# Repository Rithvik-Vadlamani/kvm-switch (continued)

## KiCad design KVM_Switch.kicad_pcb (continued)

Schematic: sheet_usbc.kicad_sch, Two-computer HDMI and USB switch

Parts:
C10, C11, C12, C13, C14, C15: 0.1uF; C_0402_1005Metric; Voltage 50V; MPN CC0402KRX7R9BB104; LCSC Part C131394
C47, C48: 100nF; C_0402_1005Metric; Voltage 50V; MPN CC0402KRX7R9BB104; LCSC Part C131394
C49, C50: 1uF; C_0603_1608Metric; Voltage 16V; MPN CL10B105KO8NNNC; LCSC Part C59782
J1, J2: USB4105-GF-A-120; USB_C_Receptacle_GCT_USB4105-xx-A_16P_TopMnt_Horizontal; MPN USB4105-GF-A-120; LCSC Part C5184243
J_HDMI_C1_MON1: HDMI_A_1.4; Assembly_J_HDMI_C1_MON1; MPN 2086581001; LCSC Part C916313
J_HDMI_C1_MON2: HDMI_A_1.4; Assembly_J_HDMI_C1_MON2; MPN 2086581001; LCSC Part C916313
J_HDMI_C2_MON1: HDMI_A_1.4; Assembly_J_HDMI_C2_MON1; MPN 2086581001; LCSC Part C916313
J_HDMI_C2_MON2: HDMI_A_1.4; Assembly_J_HDMI_C2_MON2; MPN 2086581001; LCSC Part C916313
J_HDMI_MON1: HDMI_A_1.4; Assembly_J_HDMI_MON1; MPN 2086581001; LCSC Part C916313
J_HDMI_MON2: HDMI_A_1.4; Assembly_J_HDMI_MON2; MPN 2086581001; LCSC Part C916313
R6, R14, R15, R16: 47k; R_0402_1005Metric; Tolerance 1%; MPN 0402WGF4702TCE; LCSC Part C25792
R7, R8, R9, R10: 5.1k; R_0402_1005Metric; Tolerance 1%; MPN 0402WGF5101TCE; LCSC Part C25905
R17, R18, R19, R20: 100k; R_0402_1005Metric; Tolerance 1%; MPN 0402WGF1003TCE; LCSC Part C25741
R43, R45: 10k; R_0402_1005Metric; Tolerance 1%; MPN 0402WGF1002TCE; LCSC Part C25744
R44: 10k; Assembly_R44; Tolerance 1%; MPN 0402WGF1002TCE; LCSC Part C25744
R46: 10k; Assembly_R46; Tolerance 1%; MPN 0402WGF1002TCE; LCSC Part C25744
R47, R48: 210k; R_0402_1005Metric; Tolerance 1%; MPN AF0402FR-07210KL; LCSC Part C20143942
U4, U5, U7, U11, U12, U13, U14, U15, U16, U17, U18, U19: TPD4E02B04DQA; USON-10_2.5x1.0mm_P0.5mm_Assembly; MPN TPD4E02B04DQAR; LCSC Part C106794
U6, U8: HD3SS215IRTQR; QFN-56-1EP_8x8mm_P0.5mm_EP4.5x5.2mm_ThermalVias; MPN HD3SS215IRTQT; LCSC Part C2674402
U24, U25, U26, U27, U28, U29, U30, U31: TPD4E05U06DQAR; USON-10_2.5x1.0mm_P0.5mm_Assembly; MPN TPD4E05U06DQAR; LCSC Part C138714
U32, U33: TPS2553DBVR; SOT-23-6; MPN TPS2553DBVR; LCSC Part C55266

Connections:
+3.3V: C10.1, C11.1, C12.1, C13.1, C14.1, C15.1, R43.1, R45.1, U6.19 (VDD), U6.55 (VDD), U8.19 (VDD), U8.55 (VDD), U32.3 (EN), U33.3 (EN); also elsewhere on the board
+5V: C47.1, C48.1, U32.1 (IN), U33.1 (IN); also elsewhere on the board
/USBC_Mux/C1_MON1_D0_N: J_HDMI_C1_MON1.9 (D0-), U6.47 (DA2(n)), U13.2 (IO2), U13.9 (NC)
/USBC_Mux/C1_MON1_D0_P: J_HDMI_C1_MON1.7 (D0+), U6.48 (DA2(p)), U13.1 (IO1), U13.10 (NC)
/USBC_Mux/C1_MON1_D1_N: J_HDMI_C1_MON1.6 (D1-), U6.50 (DA1(n)), U12.5 (IO4), U12.6 (NC)
/USBC_Mux/C1_MON1_D1_P: J_HDMI_C1_MON1.4 (D1+), U6.51 (DA1(p)), U12.4 (IO3), U12.7 (NC)
/USBC_Mux/C1_MON1_D2_N: J_HDMI_C1_MON1.3 (D2-), U6.53 (DA0(n)), U12.2 (IO2), U12.9 (NC)
/USBC_Mux/C1_MON1_D2_P: J_HDMI_C1_MON1.1 (D2+), U6.54 (DA0(p)), U12.1 (IO1), U12.10 (NC)
/USBC_Mux/C1_MON1_D3_N: J_HDMI_C1_MON1.12 (CK-), U6.44 (DA3(n)), U13.5 (IO4), U13.6 (NC)
/USBC_Mux/C1_MON1_D3_P: J_HDMI_C1_MON1.10 (CK+), U6.45 (DA3(p)), U13.4 (IO3), U13.7 (NC)
/USBC_Mux/C1_MON1_DDC_CLK: J_HDMI_C1_MON1.15 (SCL), U6.27 (DDCCLK_A), U26.1 (IO1)
/USBC_Mux/C1_MON1_DDC_DAT: J_HDMI_C1_MON1.16 (SDA), U6.28 (DDCDAT_A), U26.2 (IO2)
/USBC_Mux/C1_MON1_HPD: J_HDMI_C1_MON1.19 (HPD/HEAC-), R17.1, U6.16 (HPDA), U26.4 (IO3)
/USBC_Mux/C1_MON2_D0_N: J_HDMI_C1_MON2.9 (D0-), U8.51 (DA1(p)), U17.2 (IO2), U17.9 (NC)
/USBC_Mux/C1_MON2_D0_P: J_HDMI_C1_MON2.7 (D0+), U8.50 (DA1(n)), U17.1 (IO1), U17.10 (NC)
/USBC_Mux/C1_MON2_D1_N: J_HDMI_C1_MON2.6 (D1-), U8.48 (DA2(p)), U16.5 (IO4), U16.6 (NC)
/USBC_Mux/C1_MON2_D1_P: J_HDMI_C1_MON2.4 (D1+), U8.47 (DA2(n)), U16.4 (IO3), U16.7 (NC)
/USBC_Mux/C1_MON2_D2_N: J_HDMI_C1_MON2.3 (D2-), U8.45 (DA3(p)), U16.2 (IO2), U16.9 (NC)
/USBC_Mux/C1_MON2_D2_P: J_HDMI_C1_MON2.1 (D2+), U8.44 (DA3(n)), U16.1 (IO1), U16.10 (NC)
/USBC_Mux/C1_MON2_D3_N: J_HDMI_C1_MON2.12 (CK-), U8.54 (DA0(p)), U17.5 (IO4), U17.6 (NC)
/USBC_Mux/C1_MON2_D3_P: J_HDMI_C1_MON2.10 (CK+), U8.53 (DA0(n)), U17.4 (IO3), U17.7 (NC)
/USBC_Mux/C1_MON2_DDC_CLK: J_HDMI_C1_MON2.15 (SCL), U8.27 (DDCCLK_A), U28.1 (IO1)
/USBC_Mux/C1_MON2_DDC_DAT: J_HDMI_C1_MON2.16 (SDA), U8.28 (DDCDAT_A), U28.2 (IO2), U28.9 (NC)
/USBC_Mux/C1_MON2_HPD: J_HDMI_C1_MON2.19 (HPD/HEAC-), R19.1, U8.16 (HPDA), U28.4 (IO3)
/USBC_Mux/C2_MON1_D0_N: J_HDMI_C2_MON1.9 (D0-), U6.34 (DB2(n)), U15.2 (IO2), U15.9 (NC)
/USBC_Mux/C2_MON1_D0_P: J_HDMI_C2_MON1.7 (D0+), U6.35 (DB2(p)), U15.1 (IO1), U15.10 (NC)
/USBC_Mux/C2_MON1_D1_N: J_HDMI_C2_MON1.6 (D1-), U6.37 (DB1(n)), U14.5 (IO4), U14.6 (NC)
/USBC_Mux/C2_MON1_D1_P: J_HDMI_C2_MON1.4 (D1+), U6.38 (DB1(p)), U14.4 (IO3), U14.7 (NC)
/USBC_Mux/C2_MON1_D2_N: J_HDMI_C2_MON1.3 (D2-), U6.40 (DB0(n)), U14.2 (IO2), U14.9 (NC)
/USBC_Mux/C2_MON1_D2_P: J_HDMI_C2_MON1.1 (D2+), U6.41 (DB0(p)), U14.1 (IO1), U14.10 (NC)
/USBC_Mux/C2_MON1_D3_N: J_HDMI_C2_MON1.12 (CK-), U6.31 (DB3(n)), U15.5 (IO4), U15.6 (NC)
/USBC_Mux/C2_MON1_D3_P: J_HDMI_C2_MON1.10 (CK+), U6.32 (DB3(p)), U15.4 (IO3), U15.7 (NC)
/USBC_Mux/C2_MON1_DDC_CLK: J_HDMI_C2_MON1.15 (SCL), U6.22 (DDCCLK_B), U27.1 (IO1)
/USBC_Mux/C2_MON1_DDC_DAT: J_HDMI_C2_MON1.16 (SDA), U6.23 (DDCDAT_B), U27.2 (IO2)
/USBC_Mux/C2_MON1_HPD: J_HDMI_C2_MON1.19 (HPD/HEAC-), R18.1, U6.17 (HPDB), U27.4 (IO3)
/USBC_Mux/C2_MON2_D0_N: J_HDMI_C2_MON2.9 (D0-), U8.38 (DB1(p)), U19.2 (IO2), U19.9 (NC)
/USBC_Mux/C2_MON2_D0_P: J_HDMI_C2_MON2.7 (D0+), U8.37 (DB1(n)), U19.1 (IO1), U19.10 (NC)
/USBC_Mux/C2_MON2_D1_N: J_HDMI_C2_MON2.6 (D1-), U8.35 (DB2(p)), U18.5 (IO4), U18.6 (NC)
/USBC_Mux/C2_MON2_D1_P: J_HDMI_C2_MON2.4 (D1+), U8.34 (DB2(n)), U18.4 (IO3), U18.7 (NC)
/USBC_Mux/C2_MON2_D2_N: J_HDMI_C2_MON2.3 (D2-), U8.32 (DB3(p)), U18.2 (IO2), U18.9 (NC)
/USBC_Mux/C2_MON2_D2_P: J_HDMI_C2_MON2.1 (D2+), U8.31 (DB3(n)), U18.1 (IO1), U18.10 (NC)
/USBC_Mux/C2_MON2_D3_N: J_HDMI_C2_MON2.12 (CK-), U8.41 (DB0(p)), U19.5 (IO4), U19.6 (NC)
/USBC_Mux/C2_MON2_D3_P: J_HDMI_C2_MON2.10 (CK+), U8.40 (DB0(n)), U19.4 (IO3), U19.7 (NC)
/USBC_Mux/C2_MON2_DDC_CLK: J_HDMI_C2_MON2.15 (SCL), U8.22 (DDCCLK_B), U29.1 (IO1)
/USBC_Mux/C2_MON2_DDC_DAT: J_HDMI_C2_MON2.16 (SDA), U8.23 (DDCDAT_B), U29.2 (IO2)
/USBC_Mux/C2_MON2_HPD: J_HDMI_C2_MON2.19 (HPD/HEAC-), R20.1, U8.17 (HPDB), U29.4 (IO3)
/USBC_Mux/MON1_D0_N: J_HDMI_MON1.9 (D0-), U5.2 (IO2), U5.9 (NC), U6.9 (DC2(n))
/USBC_Mux/MON1_D0_P: J_HDMI_MON1.7 (D0+), U5.1 (IO1), U5.10 (NC), U6.8 (DC2(p))
/USBC_Mux/MON1_D1_N: J_HDMI_MON1.6 (D1-), U4.5 (IO4), U4.6 (NC), U6.6 (DC1(n))
/USBC_Mux/MON1_D1_P: J_HDMI_MON1.4 (D1+), U4.4 (IO3), U4.7 (NC), U6.5 (DC1(p))
/USBC_Mux/MON1_D2_N: J_HDMI_MON1.3 (D2-), U4.2 (IO2), U4.9 (NC), U6.3 (DC0(n))
/USBC_Mux/MON1_D2_P: J_HDMI_MON1.1 (D2+), U4.1 (IO1), U4.10 (NC), U6.2 (DC0(p))
/USBC_Mux/MON1_D3_N: J_HDMI_MON1.12 (CK-), U5.5 (IO4), U5.6 (NC), U6.12 (DC3(n))
/USBC_Mux/MON1_D3_P: J_HDMI_MON1.10 (CK+), U5.4 (IO3), U5.7 (NC), U6.11 (DC3(p))
/USBC_Mux/MON1_DDC_CLK: J_HDMI_MON1.15 (SCL), R6.1, U6.18 (DDCCLK_C), U30.1 (IO1)
/USBC_Mux/MON1_DDC_DAT: J_HDMI_MON1.16 (SDA), R14.1, U6.26 (DDCDAT_C), U30.2 (IO2)
/USBC_Mux/MON1_HPD: J_HDMI_MON1.19 (HPD/HEAC-), U6.15 (HPDC), U30.4 (IO3)
/USBC_Mux/MON2_D0_N: J_HDMI_MON2.9 (D0-), U8.5 (DC1(p)), U11.2 (IO2), U11.9 (NC)
/USBC_Mux/MON2_D0_P: J_HDMI_MON2.7 (D0+), U8.6 (DC1(n)), U11.1 (IO1), U11.10 (NC)
/USBC_Mux/MON2_D1_N: J_HDMI_MON2.6 (D1-), U7.5 (IO4), U7.6 (NC), U8.8 (DC2(p))
/USBC_Mux/MON2_D1_P: J_HDMI_MON2.4 (D1+), U7.4 (IO3), U7.7 (NC), U8.9 (DC2(n))
/USBC_Mux/MON2_D2_N: J_HDMI_MON2.3 (D2-), U7.2 (IO2), U7.9 (NC), U8.11 (DC3(p))
/USBC_Mux/MON2_D2_P: J_HDMI_MON2.1 (D2+), U7.1 (IO1), U7.10 (NC), U8.12 (DC3(n))
/USBC_Mux/MON2_D3_N: J_HDMI_MON2.12 (CK-), U8.2 (DC0(p)), U11.5 (IO4), U11.6 (NC)
/USBC_Mux/MON2_D3_P: J_HDMI_MON2.10 (CK+), U8.3 (DC0(n)), U11.4 (IO3), U11.7 (NC)
/USBC_Mux/MON2_DDC_CLK: J_HDMI_MON2.15 (SCL), R15.1, U8.18 (DDCCLK_C), U31.1 (IO1)
/USBC_Mux/MON2_DDC_DAT: J_HDMI_MON2.16 (SDA), R16.1, U8.26 (DDCDAT_C), U31.2 (IO2)
/USBC_Mux/MON2_HPD: J_HDMI_MON2.19 (HPD/HEAC-), U8.15 (HPDC), U31.4 (IO3)
GND: C10.2, C11.2, C12.2, C13.2, C14.2, C15.2, C47.2, C48.2, C49.2, C50.2, J1.A1 (GND), J1.A12 (GND), J1.B1 (GND), J1.B12 (GND), J1.SH (SHIELD), J2.A1 (GND), J2.A12 (GND), J2.B1 (GND), J2.B12 (GND), J2.SH (SHIELD), J_HDMI_C1_MON1.2 (D2S), J_HDMI_C1_MON1.5 (D1S), J_HDMI_C1_MON1.8 (D0S), J_HDMI_C1_MON1.11 (CKS), J_HDMI_C1_MON1.17 (GND), J_HDMI_C1_MON1.SH, J_HDMI_C1_MON2.2 (D2S), J_HDMI_C1_MON2.5 (D1S), J_HDMI_C1_MON2.8 (D0S), J_HDMI_C1_MON2.11 (CKS), J_HDMI_C1_MON2.17 (GND), J_HDMI_C1_MON2.SH, J_HDMI_C2_MON1.2 (D2S), J_HDMI_C2_MON1.5 (D1S), J_HDMI_C2_MON1.8 (D0S), J_HDMI_C2_MON1.11 (CKS), J_HDMI_C2_MON1.17 (GND), J_HDMI_C2_MON1.SH, J_HDMI_C2_MON2.2 (D2S), J_HDMI_C2_MON2.5 (D1S), J_HDMI_C2_MON2.8 (D0S), J_HDMI_C2_MON2.11 (CKS), J_HDMI_C2_MON2.17 (GND), J_HDMI_C2_MON2.SH, J_HDMI_MON1.2 (D2S), J_HDMI_MON1.5 (D1S), J_HDMI_MON1.8 (D0S), J_HDMI_MON1.11 (CKS), J_HDMI_MON1.17 (GND), J_HDMI_MON1.SH, J_HDMI_MON2.2 (D2S), J_HDMI_MON2.5 (D1S), J_HDMI_MON2.8 (D0S), J_HDMI_MON2.11 (CKS), J_HDMI_MON2.17 (GND), J_HDMI_MON2.SH, R7.2, R8.2, R9.2, R10.2, R17.2, R18.2, R19.2, R20.2, R44.2, R46.2, R47.2, R48.2, U4.3 (G), U4.8 (G), U5.3 (G), U5.8 (G), U6.4 (GND), U6.7 (GND), U6.10 (GND), U6.33 (GND), U6.36 (GND), U6.39 (GND), U6.46 (GND), U6.49 (GND), U6.52 (GND), U6.57 (PAD), U7.3 (G), U7.8 (G), U8.4 (GND), U8.7 (GND), U8.10 (GND), U8.33 (GND), U8.36 (GND), U8.39 (GND), U8.46 (GND), U8.49 (GND), U8.52 (GND), U8.57 (PAD), U11.3 (G), U11.8 (G), U12.3 (G), U12.8 (G), U13.3 (G), U13.8 (G), U14.3 (G), U14.8 (G), U15.3 (G), U15.8 (G), U16.3 (G), U16.8 (G), U17.3 (G), U17.8 (G), U18.3 (G), U18.8 (G), U19.3 (G), U19.8 (G), U24.3 (G), U24.8 (G), U25.3 (G), U25.8 (G), U26.3 (G), U26.8 (G), U27.3 (G), U27.8 (G), U28.3 (G), U28.8 (G), U29.3 (G), U29.8 (G), U30.3 (G), U30.8 (G), U31.3 (G), U31.8 (G), U32.2 (GND), U33.2 (GND); also elsewhere on the board
HDMI_ILIM1: R47.1, U32.5 (ILIM)
HDMI_ILIM2: R48.1, U33.5 (ILIM)
HDMI_MODE_1: R43.2, R44.1, U6.1 (AUX_SEL)
HDMI_MODE_2: R45.2, R46.1, U8.1 (AUX_SEL)
HDMI_MON1_5V: C49.1, J_HDMI_MON1.18 (+5V), R6.2, R14.2, U32.6 (OUT)
HDMI_MON2_5V: C50.1, J_HDMI_MON2.18 (+5V), R15.2, R16.2, U33.6 (OUT)
HOST1_CC1: J1.A5 (CC1), R9.1, U24.4 (IO3), U24.7 (NC)
HOST1_CC2: J1.B5 (CC2), R10.1, U24.5 (IO4)
HOST1_VBUS: J1.A4 (VBUS), J1.A9 (VBUS), J1.B4 (VBUS), J1.B9 (VBUS); also elsewhere on the board
HOST2_CC1: J2.A5 (CC1), R7.1, U25.4 (IO3), U25.7 (NC)
HOST2_CC2: J2.B5 (CC2), R8.1, U25.5 (IO4)
HOST2_VBUS: J2.A4 (VBUS), J2.A9 (VBUS), J2.B4 (VBUS), J2.B9 (VBUS); also elsewhere on the board
HOST_SELECT: U6.56 (Dx_SEL), U8.56 (Dx_SEL); also elsewhere on the board
MUX_RESET: U6.43 (OE), U8.43 (OE); also elsewhere on the board
USB_HOST1_N: J1.A7 (D-), J1.B7 (D-), U24.2 (IO2), U24.9 (NC); also elsewhere on the board
USB_HOST1_P: J1.A6 (D+), J1.B6 (D+), U24.1 (IO1), U24.10 (NC); also elsewhere on the board
USB_HOST2_N: J2.A7 (D-), J2.B7 (D-), U25.2 (IO2), U25.9 (NC); also elsewhere on the board
USB_HOST2_P: J2.A6 (D+), J2.B6 (D+), U25.1 (IO1), U25.10 (NC); also elsewhere on the board

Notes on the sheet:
HDMI mode: AUX_SEL must be VDD/2. 10k/10k dividers; never leave AUX_SEL floating (TI datasheet section 7.5).
External-port ESD: 5.5V-rated arrays on USB D+/D-/CC and HDMI DDC/HPD. TPD4E02B04 arrays remain on the eight TMDS conductors of each HDMI connector.
HDMI input pin 18 rails are isolated from board +5V and from each other.

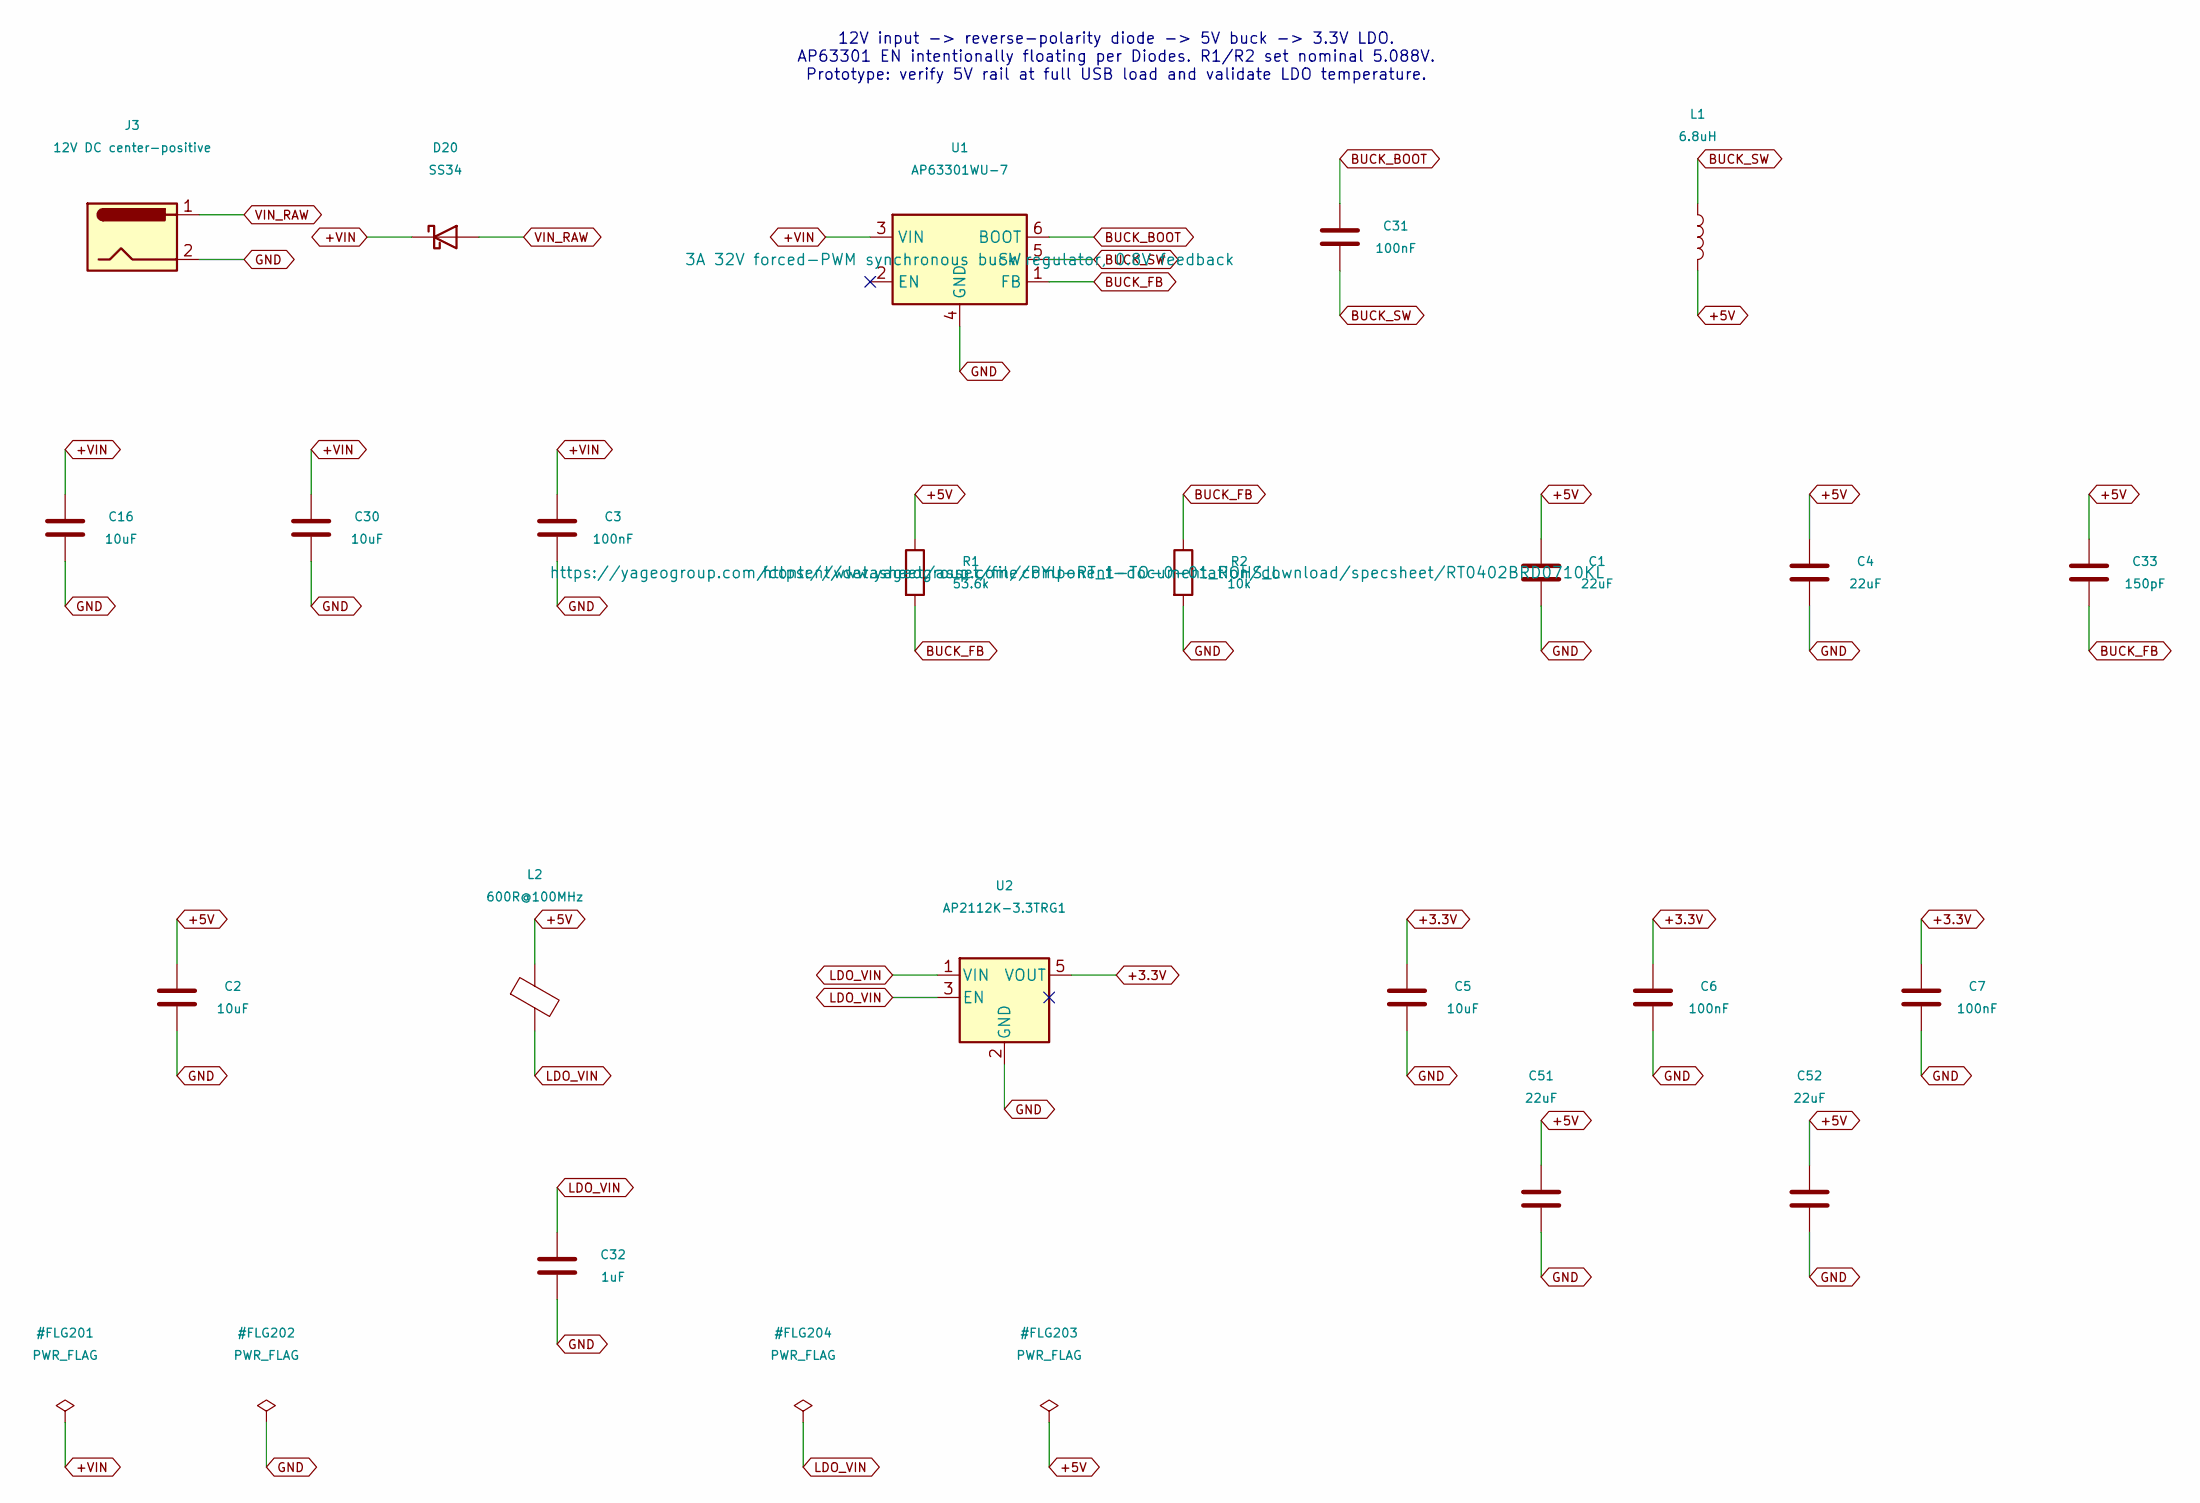
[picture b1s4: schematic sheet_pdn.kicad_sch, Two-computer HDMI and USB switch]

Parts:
C1, C4, C51, C52: 22uF; C_1206_3216Metric; Voltage 25V; MPN CL31A226KAHNNNE; LCSC Part C12891
C2, C5: 10uF; C_0805_2012Metric; Voltage 16V; MPN CL21B106KOQNNNE; LCSC Part C95841
C3, C6, C7, C31: 100nF; C_0402_1005Metric; Voltage 50V; MPN CC0402KRX7R9BB104; LCSC Part C131394
C16, C30: 10uF; C_1206_3216Metric; Voltage 50V; MPN CL31B106KBHNNNE; LCSC Part C89632
C32: 1uF; C_0603_1608Metric; Voltage 16V; MPN CL10B105KO8NNNC; LCSC Part C59782
C33: 150pF; C_0402_1005Metric; Voltage 50V; Tolerance 5%; MPN CL05C151JB5NNNC; LCSC Part C86286
D20: SS34; D_SMA; Rating 40V 3A; reverse-polarity isolation; MPN SS34; LCSC Part C8678
J3: 12V DC center-positive; BarrelJack_Wuerth_694106106102_2.0x5.5mm; MPN 694106106102; LCSC Part C7420206
L1: 6.8uH; Bourns_SRP7050TA; MPN SRP7050TA-6R8M; LCSC Part C2046414
L2: 600R@100MHz; L_0805_2012Metric; MPN BLM21PG601SN1D; LCSC Part C41556732
R1: 53.6k; R_0402_1005Metric; Tolerance 0.1%; MPN RT0402BRD0753K6L; LCSC Part C852835
R2: 10k; R_0402_1005Metric; Tolerance 0.1%; MPN RT0402BRD0710KL; LCSC Part C190095
U1: AP63301WU-7; SOT-23-6; MPN AP63301WU-7; LCSC Part C2158003
U2: AP2112K-3.3TRG1; SOT-23-5; MPN AP2112K-3.3TRG1; LCSC Part C51118

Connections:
+3.3V: C5.1, C6.1, C7.1, U2.5 (VOUT); also elsewhere on the board
+5V: C1.1, C2.1, C4.1, C33.1, C51.1, C52.1, L1.2, L2.1, R1.1; also elsewhere on the board
+VIN: C3.1, C16.1, C30.1, D20.1 (K), U1.3 (VIN)
BUCK_BOOT: C31.1, U1.6 (BST)
BUCK_FB: C33.2, R1.2, R2.1, U1.1 (FB)
BUCK_SW: C31.2, L1.1, U1.5 (SW)
GND: C1.2, C2.2, C3.2, C4.2, C5.2, C6.2, C7.2, C16.2, C30.2, C32.2, C51.2, C52.2, J3.2, R2.2, U1.4 (GND), U2.2 (GND); also elsewhere on the board
LDO_VIN: C32.1, L2.2, U2.1 (VIN), U2.3 (EN)
VIN_RAW: D20.2 (A), J3.1

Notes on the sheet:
12V input -> reverse-polarity diode -> 5V buck -> 3.3V LDO. AP63301 EN intentionally floating per Diodes. R1/R2 set nominal 5.088V. Prototype: verify 5V rail at full USB load and validate LDO temperature.

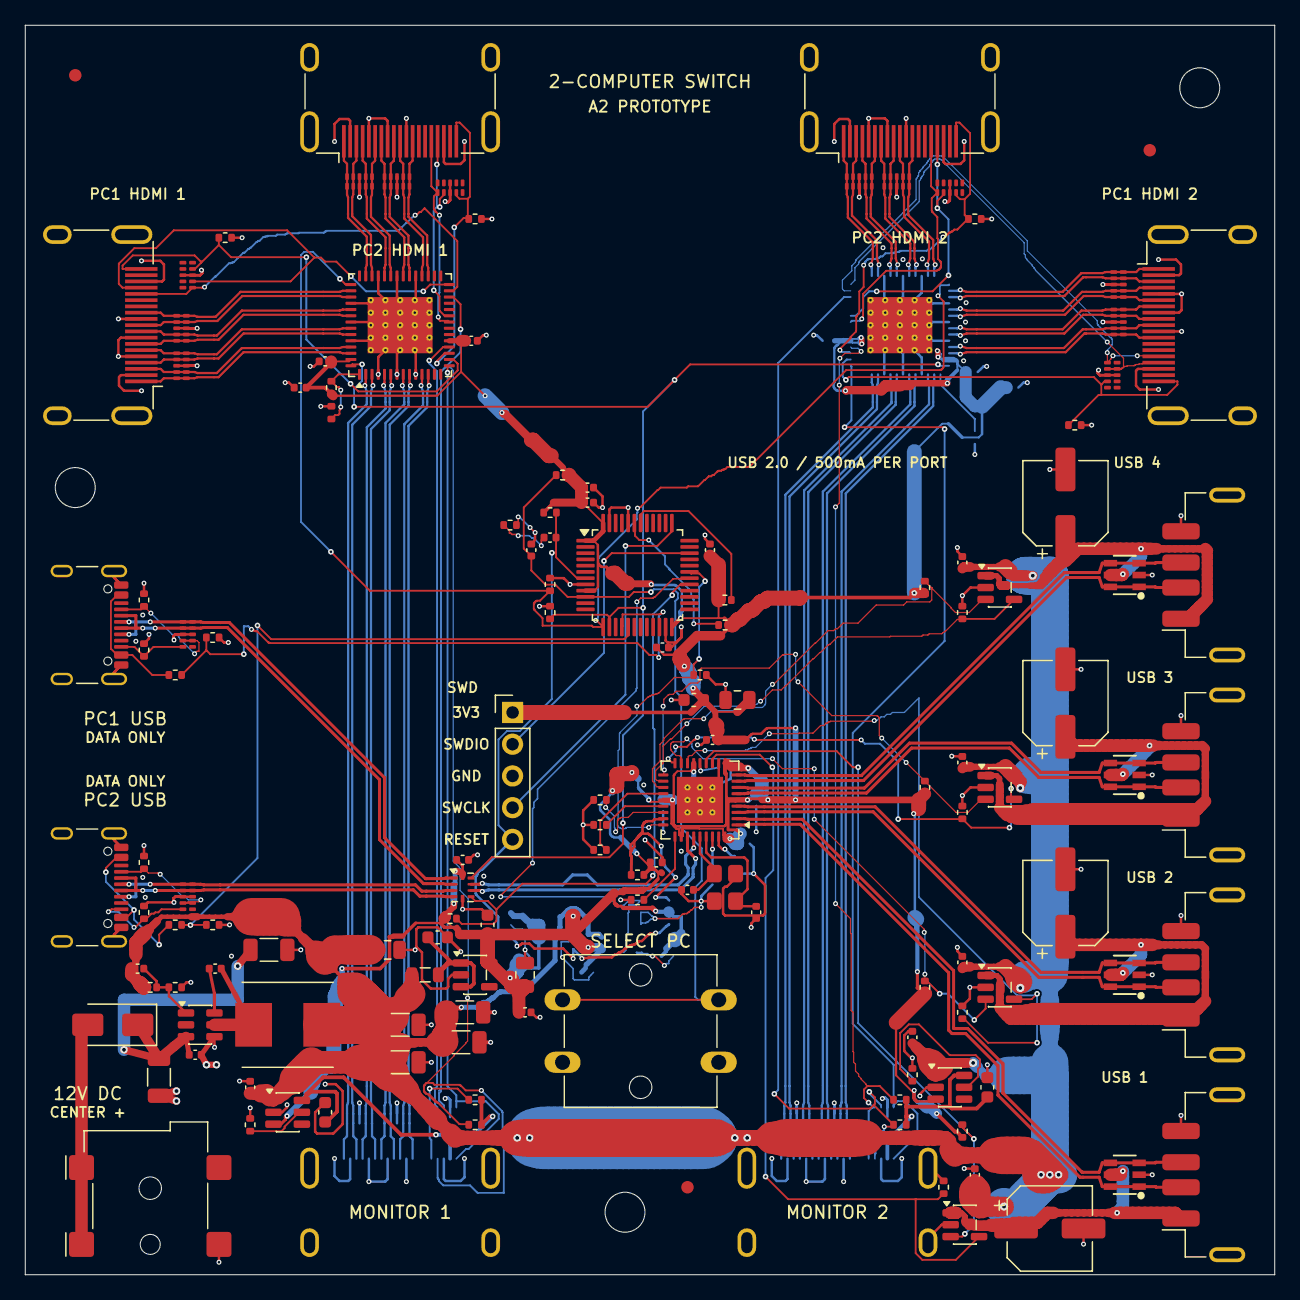
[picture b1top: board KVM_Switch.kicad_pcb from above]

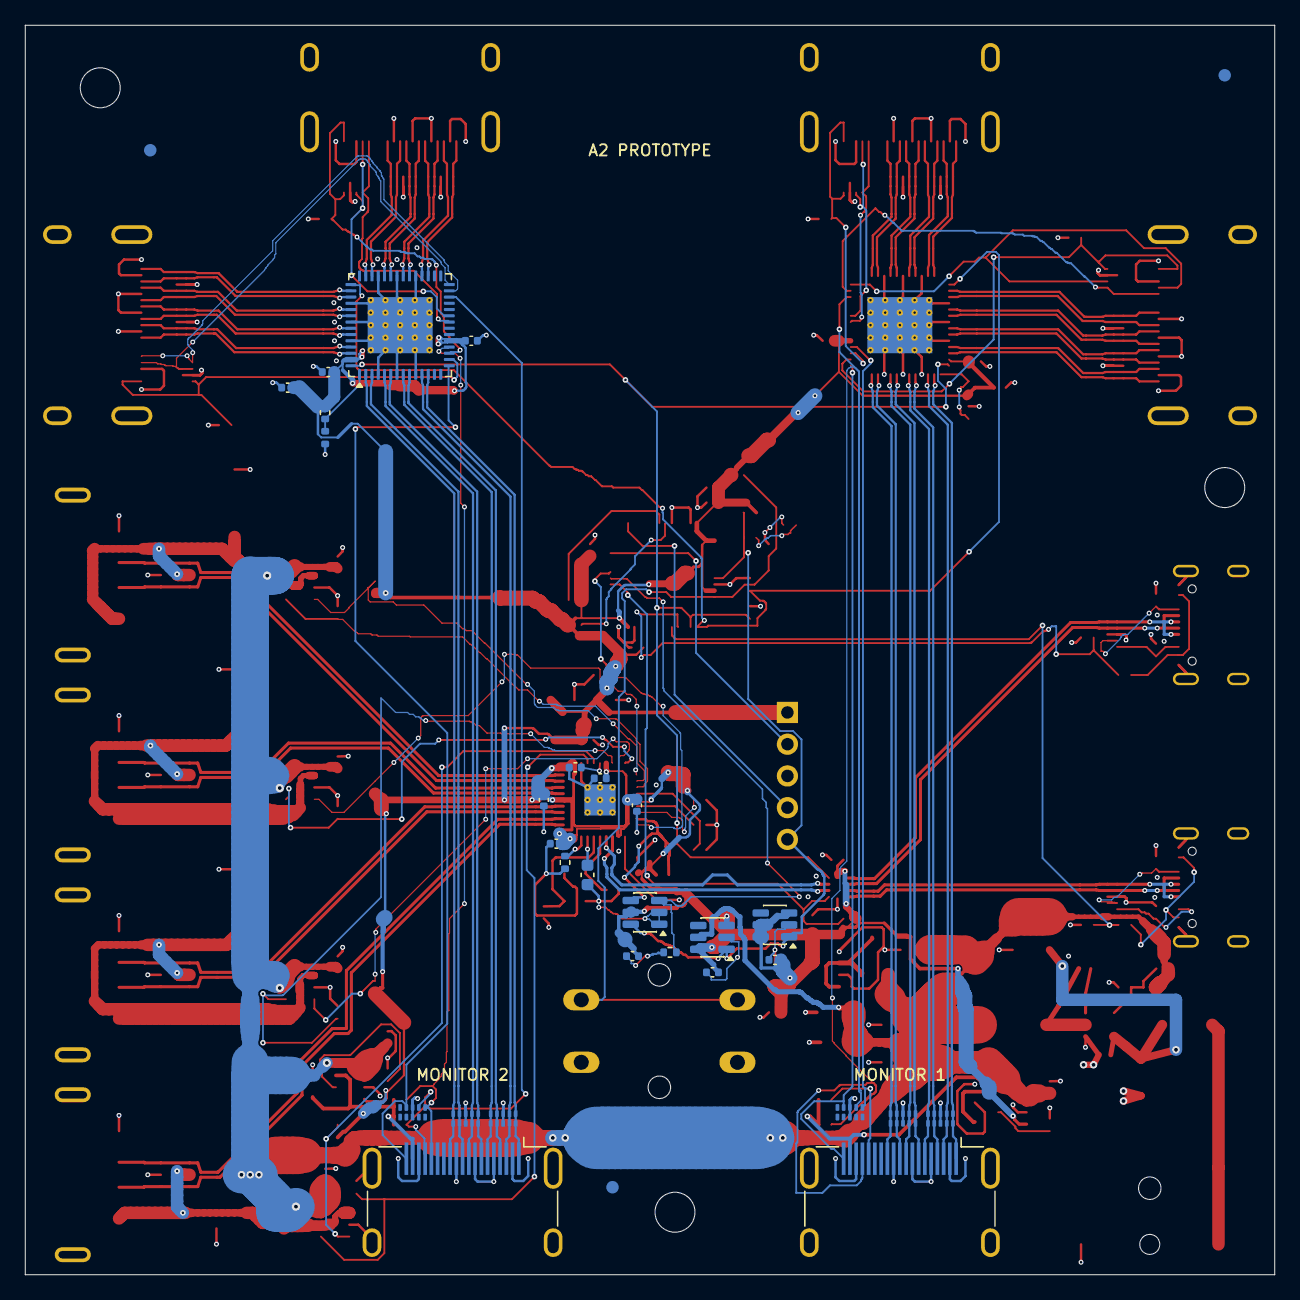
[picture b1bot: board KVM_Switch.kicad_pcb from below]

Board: 4 copper layers, 100.0 x 100.0 mm, 170 parts (31 on the bottom side), 137 nets.

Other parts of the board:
FID1, FID2, FID3, FID4, FID5, FID6: Fiducial_1mm_Mask2mm
H1, H2, H3: M3 mounting; MountingHole_3.2mm_M3

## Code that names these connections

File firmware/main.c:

/* STM32F030C8T6: HSI 8 MHz, SWD remains on PA13/PA14.
 * Register addresses/bits: ST RM0360 and cmsis-device-f0/stm32f030x8.h.
 * PA0 button (low), PA3 video OE (high), PA4 select (0=host 1),
 * PA6/7 host VBUS dividers, PA8 USB /OE, PA9 hub reset release request (U36 ANDs MCU_NRST), PA10 VBUS_DET.
 */
#include "control.h"
#ifndef REG
#define REG(a) (*(volatile uint32_t *)(a))
#endif
#define GPIOA 0x48000000u
#define RCC_AHBENR REG(0x40021014u)
#define MODER REG(GPIOA)
#define IDR REG(GPIOA+0x10u)
#define BSRR REG(GPIOA+0x18u)
#define IWDG_KR REG(0x40003000u)
#define IWDG_PR REG(0x40003004u)
#define IWDG_RLR REG(0x40003008u)
#define IWDG_SR REG(0x4000300cu)
#define VIDEO (1u<<3)
#define SELECT (1u<<4)
#define USB_OFF (1u<<8)
#define RESET_N (1u<<9)
#define VBUS (1u<<10)
static volatile uint32_t milliseconds;
void SysTick_Handler(void) { milliseconds++; }
static void outputs(const kvm_control *s) {
 /* Disconnect first; select can only change while both switches are off.
  * Hardware pulls disable both switches; U34/U35/U36 and R49 hold the hub
  * reset during supply faults, MCU reset and programming.
  */
 if (!s->video_enabled) BSRR=VIDEO<<16;
 if (!s->usb_enabled) BSRR=USB_OFF|(VBUS<<16);
 uint32_t v=(s->selected?SELECT:0u)|(s->usb_enabled?0u:USB_OFF)|
  (s->video_enabled?VIDEO:0u)|(s->hub_reset_n?RESET_N:0u)|(s->hub_vbus?VBUS:0u);
 BSRR=v|(((VIDEO|SELECT|USB_OFF|RESET_N|VBUS)&~v)<<16);
}
void Default_Handler(void) {
 BSRR=USB_OFF|((VIDEO|VBUS|RESET_N)<<16);
 for (;;) {} /* Independent watchdog resets after a fault. */
}
static void gpio_init(void) {
 RCC_AHBENR|=(1u<<17)|(1u<<18)|(1u<<19)|(1u<<22); (void)RCC_AHBENR;
 BSRR=USB_OFF|((VIDEO|SELECT|RESET_N|VBUS)<<16);
 uint32_t m=MODER;
 static const uint8_t outpins[]={3,4,8,9,10};
 for (unsigned i=0;i<sizeof(outpins);i++) {unsigned p=outpins[i]*2u;m=(m&~(3u<<p))|(1u<<p);}
 m&=~((3u<<0)|(3u<<12)|(3u<<14));
 /* Disable digital input buffers on unused pins (ST DS9773, I/O current).
  * Keep PA13/PA14 SWD. PB6/PB7 are reserved but unused by this firmware.
  */
 static const uint8_t unused_a[]={1,2,5,11,12,15};
 for (unsigned i=0;i<sizeof(unused_a);i++) m|=3u<<(unused_a[i]*2u);
 MODER=m;
 REG(0x48000400u)=0xffffffffu; /* GPIOB: no active firmware signals. */
 REG(0x48000800u)=0xffffffffu; /* GPIOC: unused, including unbonded pins. */
 REG(0x48001400u)=0xffffffffu; /* GPIOF: unused; HSI clock, no HSE crystal. */

}
int main(void) {
 gpio_init();
 REG(0xe000e014u)=7999u; REG(0xe000e018u)=0u; REG(0xe000e010u)=7u;
 /* Start first: this forces the LSI clock on before waiting for updates. */
 IWDG_KR=0xcccc; IWDG_KR=0x5555; IWDG_PR=4; IWDG_RLR=625;
 while(IWDG_SR){}
 IWDG_KR=0xaaaa; /* about 1 s at nominal 40 kHz LSI. */
 kvm_control s; kvm_init(&s,milliseconds); outputs(&s);
 uint32_t last=milliseconds; uint8_t btn_count=0, h1_count=0, h2_count=0;
 bool pressed=false,h1=false,h2=false;
 for (;;) {
  uint32_t now=milliseconds; if(now==last)continue; last=now;
  uint32_t in=IDR;
  if (!(in&1u)) {if(btn_count<30)btn_count++;} else {if(btn_count>0)btn_count--;}
  if(btn_count==30 && !pressed) {pressed=true;kvm_request(&s,now,s.pending^1u);}
  if(btn_count==0)pressed=false;
  if(in&(1u<<6)) {if(h1_count<20)h1_count++;} else {if(h1_count)h1_count--;}
  if(in&(1u<<7)) {if(h2_count<20)h2_count++;} else {if(h2_count)h2_count--;}
  if(h1_count==20)h1=true;
  if(h1_count==0)h1=false;
  if(h2_count==20)h2=true;
  if(h2_count==0)h2=false;
  kvm_tick(&s,now,h1,h2); outputs(&s); IWDG_KR=0xaaaa;
 }
}
